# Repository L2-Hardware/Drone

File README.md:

# Drone

# Custom 5-Inch Quadcopter Project

Welcome to the main repository of our custom-built 5-inch FPV drone. This project is a collaborative effort to design, build, and program a high-performance quadcopter completely from scratch, bridging custom mechanical engineering with bespoke hardware and software design.

## Project Overview

Instead of relying on off-the-shelf Flight Controllers (FC) or pre-compiled firmware like Betaflight/ArduPilot, this project aims to build the core systems from the ground up to deeply understand drone flight dynamics, sensor fusion, and real-time embedded systems.

The project is divided into three main domains:
*   **Mechanics & Frame:** Custom 5-inch carbon fiber frame designed from scratch (designed by [Friend's Name]).
*   **Hardware (FC PCB):** A custom-designed Flight Controller board based on the STM32 architecture.
*   **Firmware (MCU):** A custom RTOS-based flight control software written in C/C++.

## System Architecture

*   **Power & Propulsion:** 6S LiPo Battery, custom 4-in-1 ESC (`Hardware/Kicad/ESCV00`, AM32 firmware), and 4x Brushless Motors (2207/2306).
*   **Radio Control:** custom ExpressLRS (ELRS) 2.4GHz receiver (`Hardware/Kicad/RXV00`, ESP32-C3 + SX1281) communicating via CRSF protocol for ultra-low latency.
*   **Video System (FPV):** custom analog 5.8GHz VTx (`Hardware/Kicad/VTXV00`, RTC6705 + RFPA5542) with on-board OSD (AT7456E) on the FC.
*   **Brain:** Custom STM32 Flight Controller (See `/Hardware` and `/Firmware` folders).

## Repository Structure

*   `/Mechanics` - 3D models, CAD files, and CNC routing paths for the frame.
*   `/Hardware` - KiCad projects: flight controller (FCV00), 4-in-1 ESC (ESCV00), ELRS receiver (RXV00), video transmitter (VTXV00).
*   `/Firmware` - STM32 source code, RTOS configuration, and PID algorithms.

## Status
*Active Development* - Currently designing the FC PCB and prototyping the RTOS task scheduler.

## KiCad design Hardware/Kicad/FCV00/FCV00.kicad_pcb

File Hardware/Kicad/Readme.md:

# KiCad projects - drone electronics

## Libraries

If you want a local copy of Kicad Libraries for each board project, inside the KiCad directory run:

git submodule add https://github.com/Loredati-svg/Kicad_Library.git
git commit -m "Added Kicad Libs submodule"
git push

If you don't want a local copy of the libraries for each project but you are ok with having a single local copy of it in a different folder and want to link to it from the board project folder, just run the "bring_libs.bat".
This will create a junction link.

### Part convention (same as B0_EE)

All the parts used by the four boards are in the shared [Kicad_Libs](https://github.com/L2-Hardware/Kicad_Libs)
(`${KIPRJMOD}/../KiCad_Libs/<eLib>`). Every real part is named after its manufacturer part number, and the
symbol, footprint, 3D model and datasheet all carry that name:

```
<eLib>.kicad_sym             symbol      <eLib>:STM32F405RGT6
<eLib>.pretty/               footprint   STM32F405RGT6.kicad_mod
<eLib>.3dshapes/             3D model    STM32F405RGT6.step
datasheet/                   datasheet   STM32F405RGT6.pdf  (README.md: manufacturer and full ordering code)
```

Symbols carry the five standard fields only: Reference, Value (= part name), Footprint, Datasheet
(`${KIPRJMOD}/../KiCad_Libs/<eLib>/datasheet/<part>.pdf`) and Description. Plain passives without a part number
(R, C, LED, L) keep the generic symbol with the value and a package footprint. Test points, mounting holes and
solder jumpers are copper only: no 3D model and not in the BOM.

Where the parts come from:
* **Footprints**: official KiCad libraries, renamed after the part. **3D models**: STEP from KiCad 10.
* **Symbols**: generated in a single style. Pin tables come from the official KiCad symbol of the same part where
  KiCad has one. Otherwise they come from the vendor datasheet (see "Verify before ordering boards").

## Boards

| Project | Board | Size / layers | Main parts |
|---|---|---|---|
| `FCV00` | Flight controller | 36x36 mm, 30.5 mm M3 pattern (4 mm holes for grommets), 4 layers | STM32F405RGT6, ICM-42688-P, LPS22DF, AT7456E OSD, W25Q128JV, 2x TPS54360B (5V 3A / 10V 2A), 2x AP2112K-3.3, USB-C |
| `ESCV00` | 4-in-1 ESC (AM32) | 42x42 mm, 30.5 mm M3 pattern, 6 layers 2 oz recommended | 4x (STM32F051K8U6 or AT32F421K8U7 + DRV8300D + 6x BSZ018N04LS6), 0.25 mOhm shunt + INA181A3, LMR16006 10V gate rail |
| `RXV00` | ExpressLRS 2.4 GHz receiver | 22x14 mm, 4 layers | ESP32-C3FH4 + SX1281, u.FL |
| `VTXV00` | 5.8 GHz analog VTX | 27x27 mm, 20x20 mm M2 pattern, 4 layers | RTC6705 + RFPA5542 (~25 dBm), STM32F031G6U6 / GD32F130G6U6 (OpenVTx) |

```
 6S LiPo ──XT60──► ESCV00 ──(JST-SH 8: VBAT GND CURR TLM M1..M4)──► FCV00 ──(JST-SH 4: 5V GND TX RX)──► RXV00 ── 2.4 GHz antenna
                   │  4x BLDC motors                                  │  ├─(JST-SH 6: 10V 5V GND VIDEO TX RX)──► VTXV00 ── 5.8 GHz antenna
                   └──────────────────────────────────────────────────┘  ├─(JST-SH 3: PWR GND VIDEO)◄── analog FPV camera (bought)
                                                                         ├─ GPS / compass port, AUX UART port, LED strip, buzzer
                                                                         └─ USB-C (configuration / DFU)
```

The connectors are pin-matched, so the harnesses are 1:1 JST-SH cables. Power the FC from the ESC harness only,
not from separate battery wires. Otherwise part of the motor return current flows through the JST ground wire
and bypasses the current shunt.

Bought parts that are not designed here: motors, battery, camera, propellers, antennas, frame.

### Each project contains
* `<NAME>.kicad_sch` - hierarchical schematic (root page = overview + design notes, one sub-sheet per block)
* `<NAME>.kicad_pcb` - board outline, mounting holes, layer count, GND plane on In1, every footprint loaded with
  its nets and linked to its symbol (footprints are parked next to the outline, grouped by sheet)
* `<NAME>.kicad_pro` - net classes (power / gate / RF 50 ohm / USB ...) and JLCPCB-compatible minimum rules
* `<NAME>_BOM.csv` - grouped BOM exported from the schematic with `kicad-cli` (Value = part number for real parts)
* `RXV00/RXV00_hardware.json` - ExpressLRS hardware layout for the receiver

## Validation done
* Every schematic was exported with `kicad-cli`. KiCad's connectivity matches the intended netlist exactly (no
  merged or split nets).
* Every symbol pin maps to a footprint pad. Every footprint pad that needs a net has one.
* KiCad 10 `kicad-cli`: no symbol/footprint library mismatch in ERC or DRC, and schematic/PCB parity is clean
  (fields, footprints, BOM/DNP attributes).

## Verify before ordering boards
Parts whose pin table was typed from a datasheet. Check them against the latest datasheet:

| Part | What to check |
|---|---|
| AT7456E | Uses the MAX7456 pinout. Check the HTSSOP exposed-pad size. |
| SX1281IMLTRT | Pin table from Semtech DS rev 3.x. RF matching values are starting points (tune with a VNA). |
| RTC6705 | Pin table from `eRFModule/datasheet/RTC6705.pdf`. The exposed-pad size is not given (QFN-40 6x6, EP 4.6 assumed). Loop filter, output match and the BUFVDD power-control path are starting points. |
| DRV8300DRGER | Pin table from the TI datasheet. Check the RGE exposed-pad size. |
| ICM-42688-P | Pin table from the KiCad IIM-42652 symbol (same LGA-14 package). Check the RESV pins. |
| BSZ018N04LS6ATMA1 | NexFET SON3.3 land pattern reused. Compare with Infineon's PG-TSDSON-8 FL footprint. |
| TPS54360BDDAR | The compensation network is a starting point. Run TI WEBENCH for the final values. |
| X201652MOB4SI | SX1280 reference crystal: 52 MHz, +/-10 ppm. |

Part numbers that could not be found in the manufacturer catalogue: confirm or replace them before ordering.

| Part | Note |
|---|---|
| X322508MLB4SI, X201640MLB4SI, X201652MOB4SI | Not listed by YXC/LCSC. The stored datasheet is the YXC SMD3225 / SMD2016 series sheet. |
| LQM21PN150MC0 | Not in the Murata LQM21PN range (which stops below 15 uH). No datasheet stored. |
| WSLP2512R0010FEA | 1 mOhm WSLP2512: check availability; the stored datasheet is the Vishay WSLP series sheet. |
| SWPA3012S100MT, PMEG3020EH | Datasheet not stored (the vendor site blocks downloads): the Datasheet field links to it. |

Passive, crystal and LED part numbers are suggestions: confirm them (stock, load capacitance, voltage rating) at
your distributor or assembler.

## Next steps
1. Open each project, run ERC.
2. PCB: place the parts (connectors on the edges, IMU away from the bucks, short power loops), then route.
   Use 50 ohm coplanar lines on RXV00/VTXV00 and a full GND plane under the RF parts. On ESCV00, use wide
   polygons for VBAT/phases and thermal vias. Run DRC.
3. Order from JLCPCB / PCBWay: gerbers + BOM + placement file, assembly (ESC 6 layers 2 oz).
4. Bring-up order: power rails, then SWD/DFU, then each sensor, then radio links.

## Firmware notes
* **FCV00**: pin map on the root sheet (gyro SPI1 + external 32 kHz CLKIN on PB0, OSD SPI2, flash SPI3,
  motors TIM8 CH1-4 on PC6-PC9).
* **ESCV00**: AM32. With F051, use `HARDWARE_GROUP_F0_B`. With AT32F421, use `HARDWARE_GROUP_AT_B` +
  `HARDWARE_GROUP_AT_045` (same pinout as `TBS_6S_4IN1_F421`). Flash the bootloader per MCU through the SWD pads
  once.
* **RXV00**: ExpressLRS `Unified_ESP32C3_2400_RX` + `RXV00_hardware.json` (based on "Generic C3 2400").
* **VTXV00**: OpenVTx `Generic_GD32F130` pinout (populate GD32F130G6U6), or your own firmware on the STM32F031.
  Up to 25 mW EIRP is licence-free in the EU. Higher power needs an amateur radio licence.

## Regenerating
`tools/gen/` holds the scripts that produced the libraries, schematics, BOMs and PCB set-up:
`build.py` (libraries + schematics + BOM), `check.py` (connectivity check) and `pcbgen.py` (PCB set-up).
**Re-running them overwrites the project files.** They are a starting point: once you start editing in KiCad,
KiCad is the master. They still produce the old generic part names, so do not re-run them on these boards.

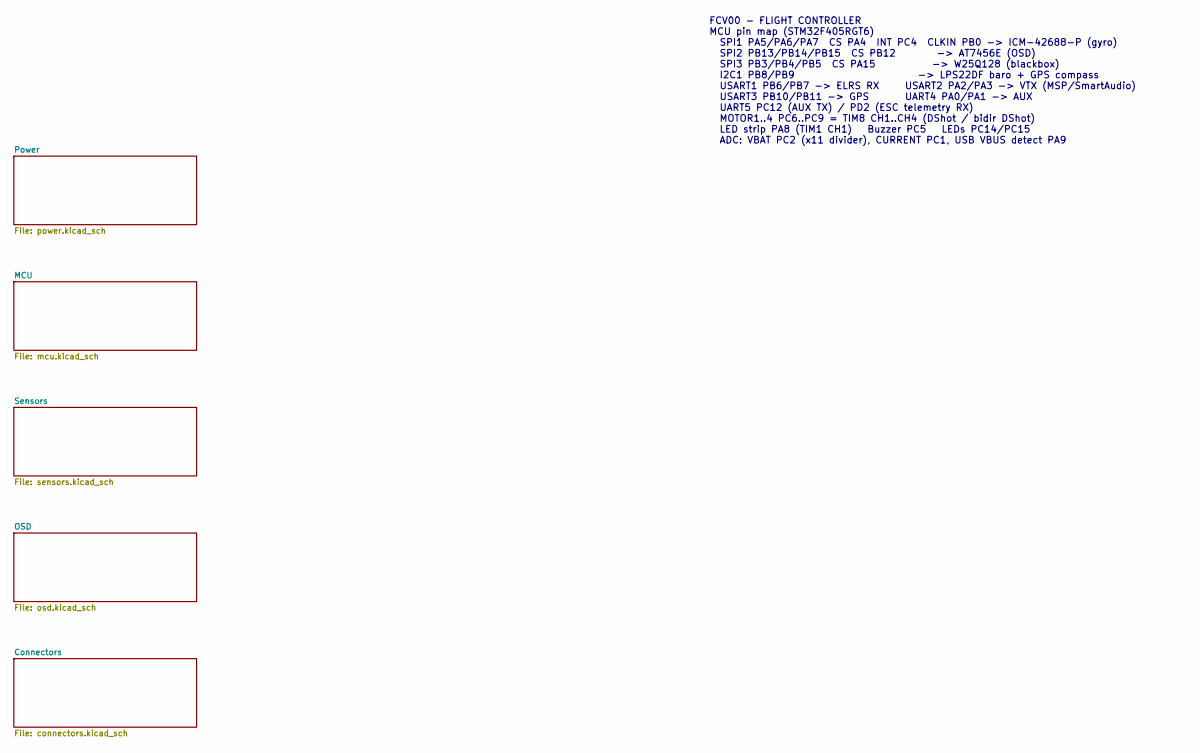
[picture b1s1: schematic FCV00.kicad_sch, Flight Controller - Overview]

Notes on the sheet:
FCV00 - FLIGHT CONTROLLER MCU pin map (STM32F405RGT6) SPI1 PA5/PA6/PA7 CS PA4 INT PC4 CLKIN PB0 -> ICM-42688-P (gyro) SPI2 PB13/PB14/PB15 CS PB12 -> AT7456E (OSD) SPI3 PB3/PB4/PB5 CS PA15 -> W25Q128 (blackbox) I2C1 PB8/PB9 -> LPS22DF baro + GPS compass USART1 PB6/PB7 -> ELRS RX USART2 PA2/PA3 -> VT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

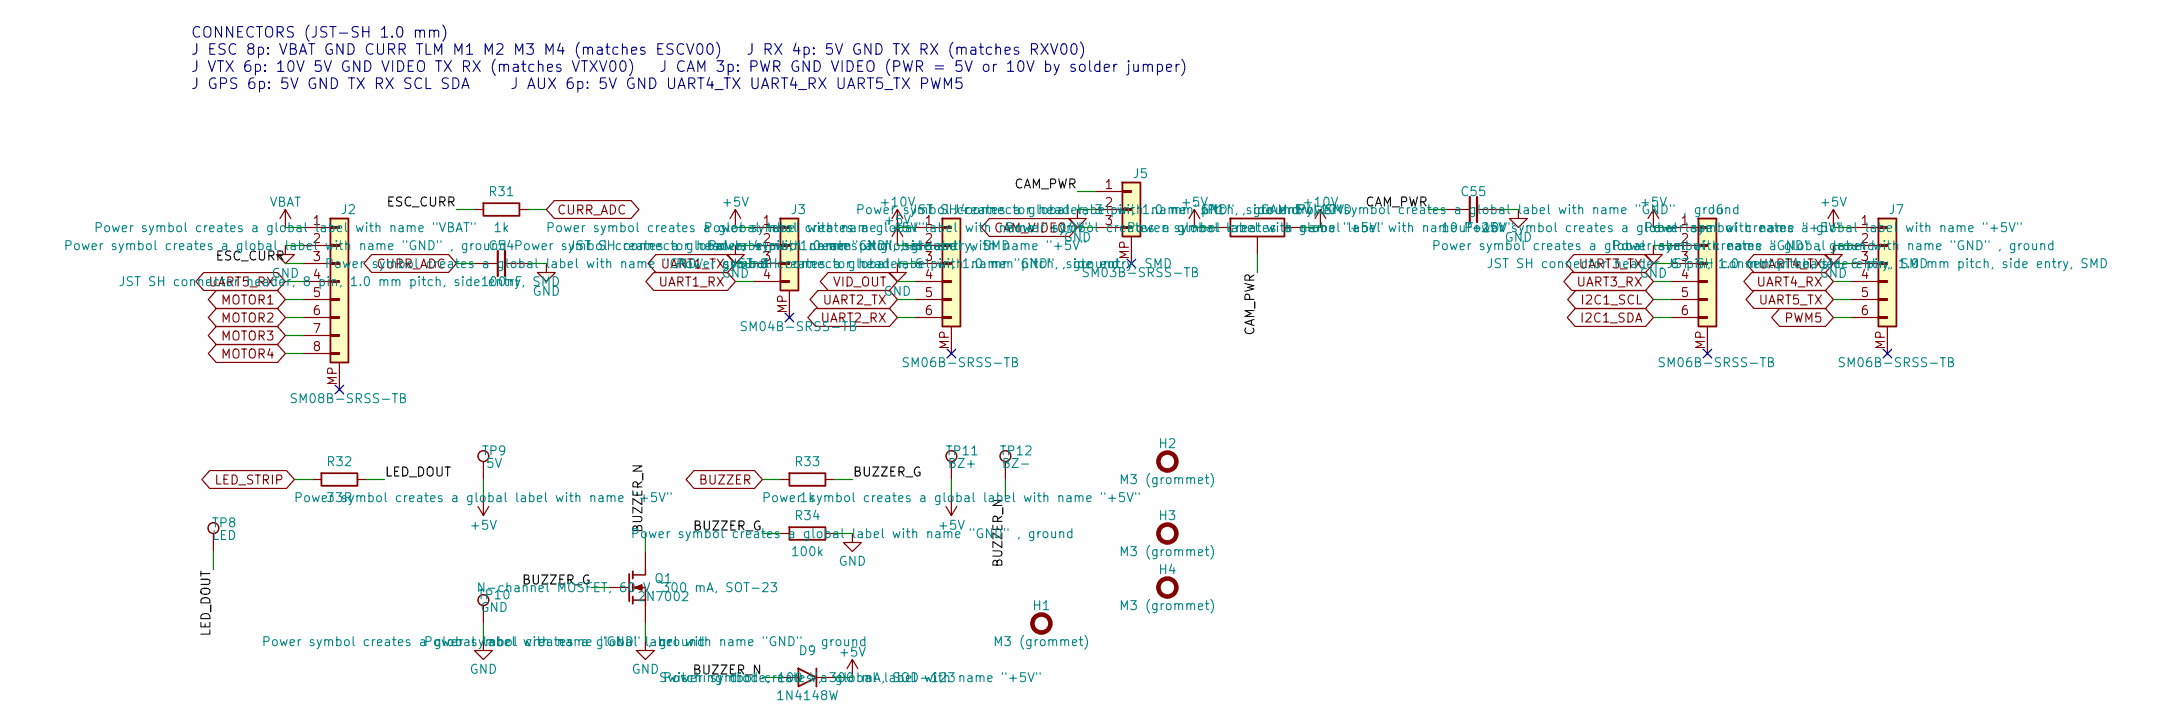
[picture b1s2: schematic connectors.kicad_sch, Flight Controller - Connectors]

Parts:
C54: 100nF; C_0402_1005Metric
C55: 10uF 25V; C_0805_2012Metric
D9: 1N4148W
H1, H2, H3, H4: M3 (grommet); MountingHole_4mm
J2: SM08B-SRSS-TB
J3: SM04B-SRSS-TB
J4, J6, J7: SM06B-SRSS-TB
J5: SM03B-SRSS-TB
JP1: CAM 5V|10V; SolderJumper-3_P1.3mm_Open_RoundedPad1.0x1.5mm
Q1: 2N7002
R31, R33: 1k; R_0402_1005Metric
R32: 33R; R_0402_1005Metric
R34: 100k; R_0402_1005Metric
TP8: LED; TestPoint_Pad_2.0x2.0mm
TP9: 5V; TestPoint_Pad_2.0x2.0mm
TP10: GND; TestPoint_Pad_2.0x2.0mm
TP11: BZ+; TestPoint_Pad_2.0x2.0mm
TP12: BZ-; TestPoint_Pad_2.0x2.0mm

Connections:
+5V: D9.1 (K), J3.1, J4.2, J6.1, J7.1, JP1.1 (A), TP9.1, TP11.1; also elsewhere on the board
+10V: J4.1, JP1.3 (B); also elsewhere on the board
/Connectors/BUZZER_G: Q1.1 (G), R33.2, R34.1
/Connectors/BUZZER_N: D9.2 (A), Q1.3 (D), TP12.1
/Connectors/CAM_PWR: C55.1, J5.1, JP1.2 (C)
/Connectors/ESC_CURR: J2.3, R31.1
/Connectors/LED_DOUT: R32.2, TP8.1
BUZZER: R33.1; also elsewhere on the board
CAM_VIDEO: J5.3; also elsewhere on the board
CURR_ADC: C54.1, R31.2; also elsewhere on the board
GND: C54.2, C55.2, J2.2, J3.2, J4.3, J5.2, J6.2, J7.2, Q1.2 (S), R34.2, TP10.1; also elsewhere on the board
I2C1_SCL: J6.5; also elsewhere on the board
I2C1_SDA: J6.6; also elsewhere on the board
LED_STRIP: R32.1; also elsewhere on the board
MOTOR1: J2.5; also elsewhere on the board
MOTOR2: J2.6; also elsewhere on the board
MOTOR3: J2.7; also elsewhere on the board
MOTOR4: J2.8; also elsewhere on the board
PWM5: J7.6; also elsewhere on the board
UART1_RX: J3.4; also elsewhere on the board
UART1_TX: J3.3; also elsewhere on the board
UART2_RX: J4.6; also elsewhere on the board
UART2_TX: J4.5; also elsewhere on the board
UART3_RX: J6.4; also elsewhere on the board
UART3_TX: J6.3; also elsewhere on the board
UART4_RX: J7.4; also elsewhere on the board
UART4_TX: J7.3; also elsewhere on the board
UART5_RX: J2.4; also elsewhere on the board
UART5_TX: J7.5; also elsewhere on the board
VBAT: J2.1; also elsewhere on the board
VID_OUT: J4.4; also elsewhere on the board

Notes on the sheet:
CONNECTORS (JST-SH 1.0 mm) J ESC 8p: VBAT GND CURR TLM M1 M2 M3 M4 (matches ESCV00) J RX 4p: 5V GND TX RX (matches RXV00) J VTX 6p: 10V 5V GND VIDEO TX RX (matches VTXV00) J CAM 3p: PWR GND VIDEO (PWR = 5V or 10V by solder jumper) J GPS 6p: 5V GND TX RX SCL SDA J AUX 6p: 5V GND UART4_TX UART4_RX UA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

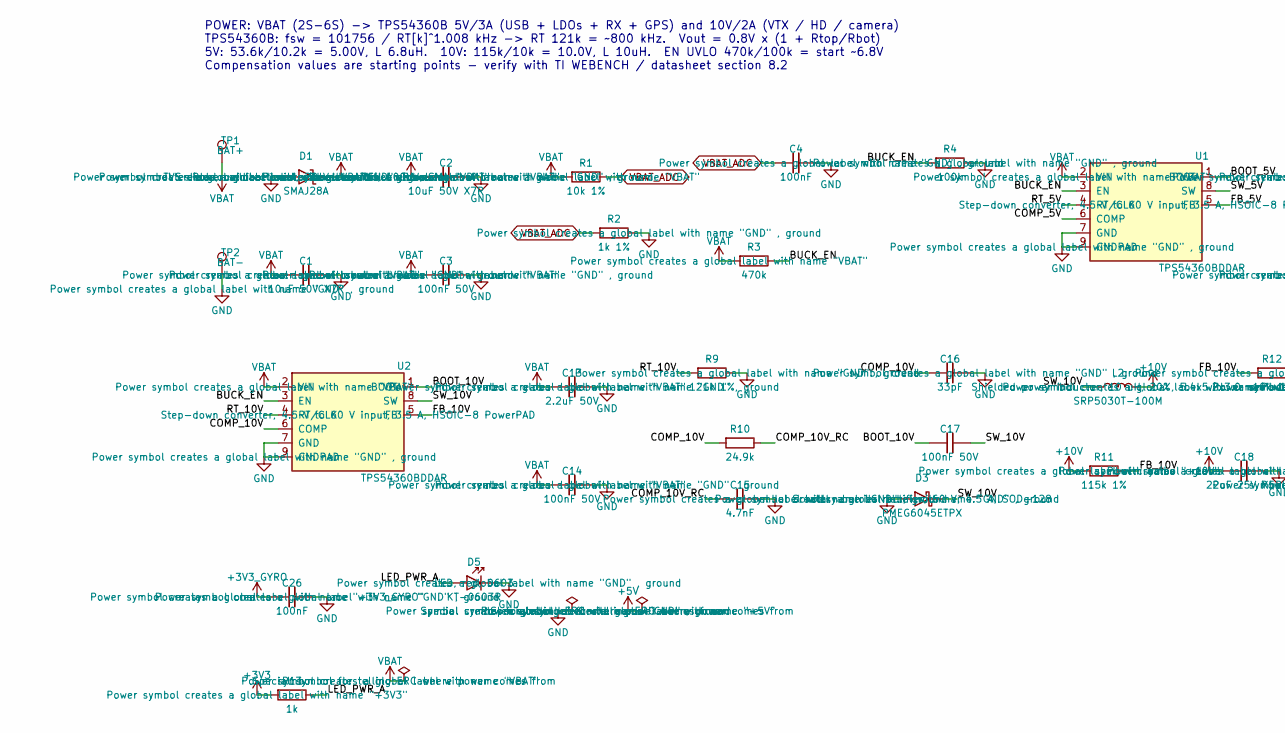
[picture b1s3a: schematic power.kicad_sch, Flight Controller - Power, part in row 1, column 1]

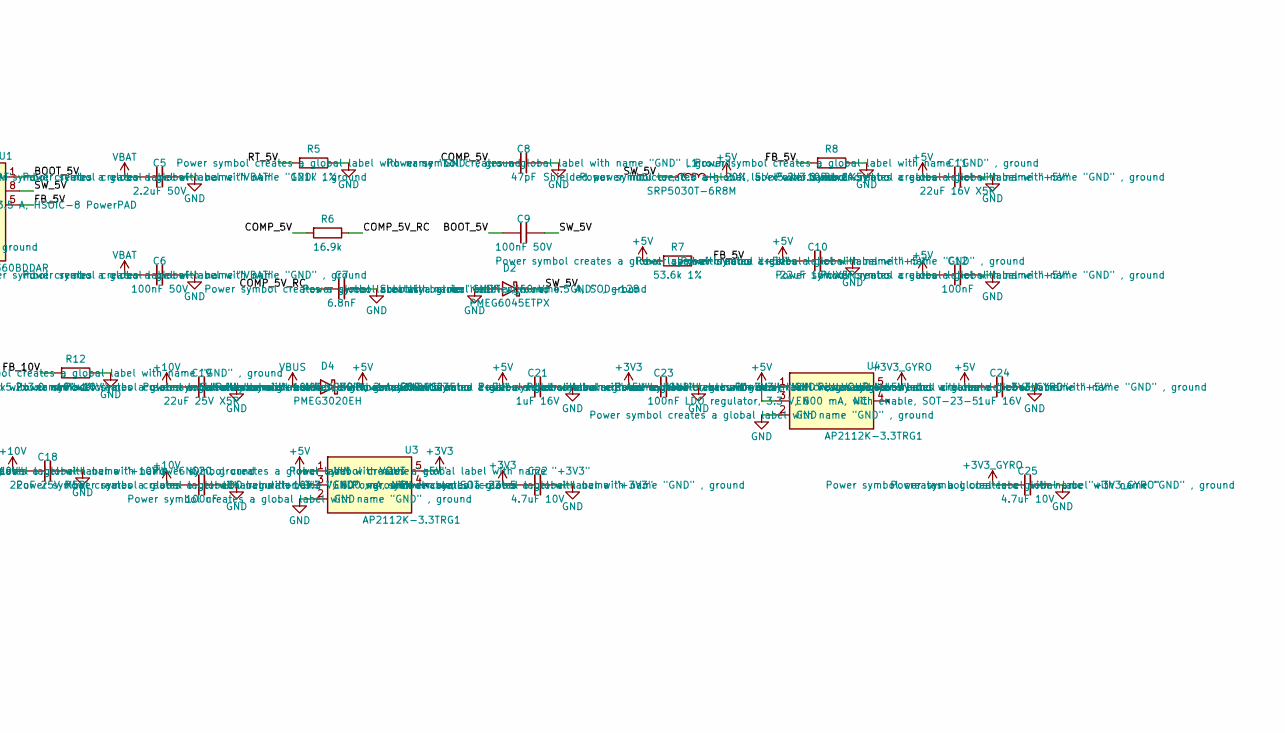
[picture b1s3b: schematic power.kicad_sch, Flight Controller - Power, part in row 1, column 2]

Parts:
C1, C2: 10uF 50V X7R; C_1206_3216Metric
C3, C6, C9, C14, C17: 100nF 50V; C_0603_1608Metric
C4, C12, C20, C23, C26: 100nF; C_0402_1005Metric
C5, C13: 2.2uF 50V; C_0805_2012Metric
C7: 6.8nF; C_0402_1005Metric
C8: 47pF; C_0402_1005Metric
C10, C11: 22uF 16V X5R; C_0805_2012Metric
C15: 4.7nF; C_0402_1005Metric
C16: 33pF; C_0402_1005Metric
C18, C19: 22uF 25V X5R; C_1206_3216Metric
C21, C24: 1uF 16V; C_0402_1005Metric
C22, C25: 4.7uF 10V; C_0603_1608Metric
D1: SMAJ28A
D2, D3: PMEG6045ETPX
D4: PMEG3020EH
D5: KT-0603R
L1: SRP5030T-6R8M
L2: SRP5030T-100M
R1, R12: 10k 1%; R_0402_1005Metric
R2: 1k 1%; R_0402_1005Metric
R3: 470k; R_0402_1005Metric
R4: 100k; R_0402_1005Metric
R5, R9: 121k 1%; R_0402_1005Metric
R6: 16.9k; R_0402_1005Metric
R7: 53.6k 1%; R_0402_1005Metric
R8: 10.2k 1%; R_0402_1005Metric
R10: 24.9k; R_0402_1005Metric
R11: 115k 1%; R_0402_1005Metric
R13: 1k; R_0402_1005Metric
TP1: BAT+; SolderPad_3x5mm
TP2: BAT-; SolderPad_3x5mm
U1, U2: TPS54360BDDAR
U3, U4: AP2112K-3.3TRG1

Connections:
+3V3: C22.1, C23.1, R13.1, U3.5 (VOUT); also elsewhere on the board
+3V3_GYRO: C25.1, C26.1, U4.5 (VOUT); also elsewhere on the board
+5V: C10.1, C11.1, C12.1, C21.1, C24.1, D4.1 (K), L1.2, R7.1, U3.1 (VIN), U3.3 (EN), U4.1 (VIN), U4.3 (EN); also elsewhere on the board
+10V: C18.1, C19.1, C20.1, L2.2, R11.1; also elsewhere on the board
/Power/BOOT_5V: C9.1, U1.1 (BOOT)
/Power/BOOT_10V: C17.1, U2.1 (BOOT)
/Power/BUCK_EN: R3.2, R4.1, U1.3 (EN), U2.3 (EN)
/Power/COMP_5V: C8.1, R6.1, U1.6 (COMP)
/Power/COMP_5V_RC: C7.1, R6.2
/Power/COMP_10V: C16.1, R10.1, U2.6 (COMP)
/Power/COMP_10V_RC: C15.1, R10.2
/Power/FB_5V: R7.2, R8.1, U1.5 (FB)
/Power/FB_10V: R11.2, R12.1, U2.5 (FB)
/Power/LED_PWR_A: D5.2 (A), R13.2
/Power/RT_5V: R5.1, U1.4 (RT/CLK)
/Power/RT_10V: R9.1, U2.4 (RT/CLK)
/Power/SW_5V: C9.2, D2.1 (K), L1.1, U1.8 (SW)
/Power/SW_10V: C17.2, D3.1 (K), L2.1, U2.8 (SW)
GND: C1.2, C2.2, C3.2, C4.2, C5.2, C6.2, C7.2, C8.2, C10.2, C11.2, C12.2, C13.2, C14.2, C15.2, C16.2, C18.2, C19.2, C20.2, C21.2, C22.2, C23.2, C24.2, C25.2, C26.2, D1.2 (A), D2.2 (A), D3.2 (A), D5.1 (K), R2.2, R4.2, R5.2, R8.2, R9.2, R12.2, TP2.1, U1.7 (GND), U1.9 (GNDPAD), U2.7 (GND), U2.9 (GNDPAD), U3.2 (GND), U4.2 (GND); also elsewhere on the board
VBAT: C1.1, C2.1, C3.1, C5.1, C6.1, C13.1, C14.1, D1.1 (K), R1.1, R3.1, TP1.1, U1.2 (VIN), U2.2 (VIN); also elsewhere on the board
VBAT_ADC: C4.1, R1.2, R2.1; also elsewhere on the board
VBUS: D4.2 (A); also elsewhere on the board

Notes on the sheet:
POWER: VBAT (2S-6S) -> TPS54360B 5V/3A (USB + LDOs + RX + GPS) and 10V/2A (VTX / HD / camera) TPS54360B: fsw = 101756 / RT[k]^1.008 kHz -> RT 121k = ~800 kHz. Vout = 0.8V x (1 + Rtop/Rbot) 5V: 53.6k/10.2k = 5.00V, L 6.8uH. 10V: 115k/10k = 10.0V, L 10uH. EN UVLO 470k/100k = start ~6.8V Compensation 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

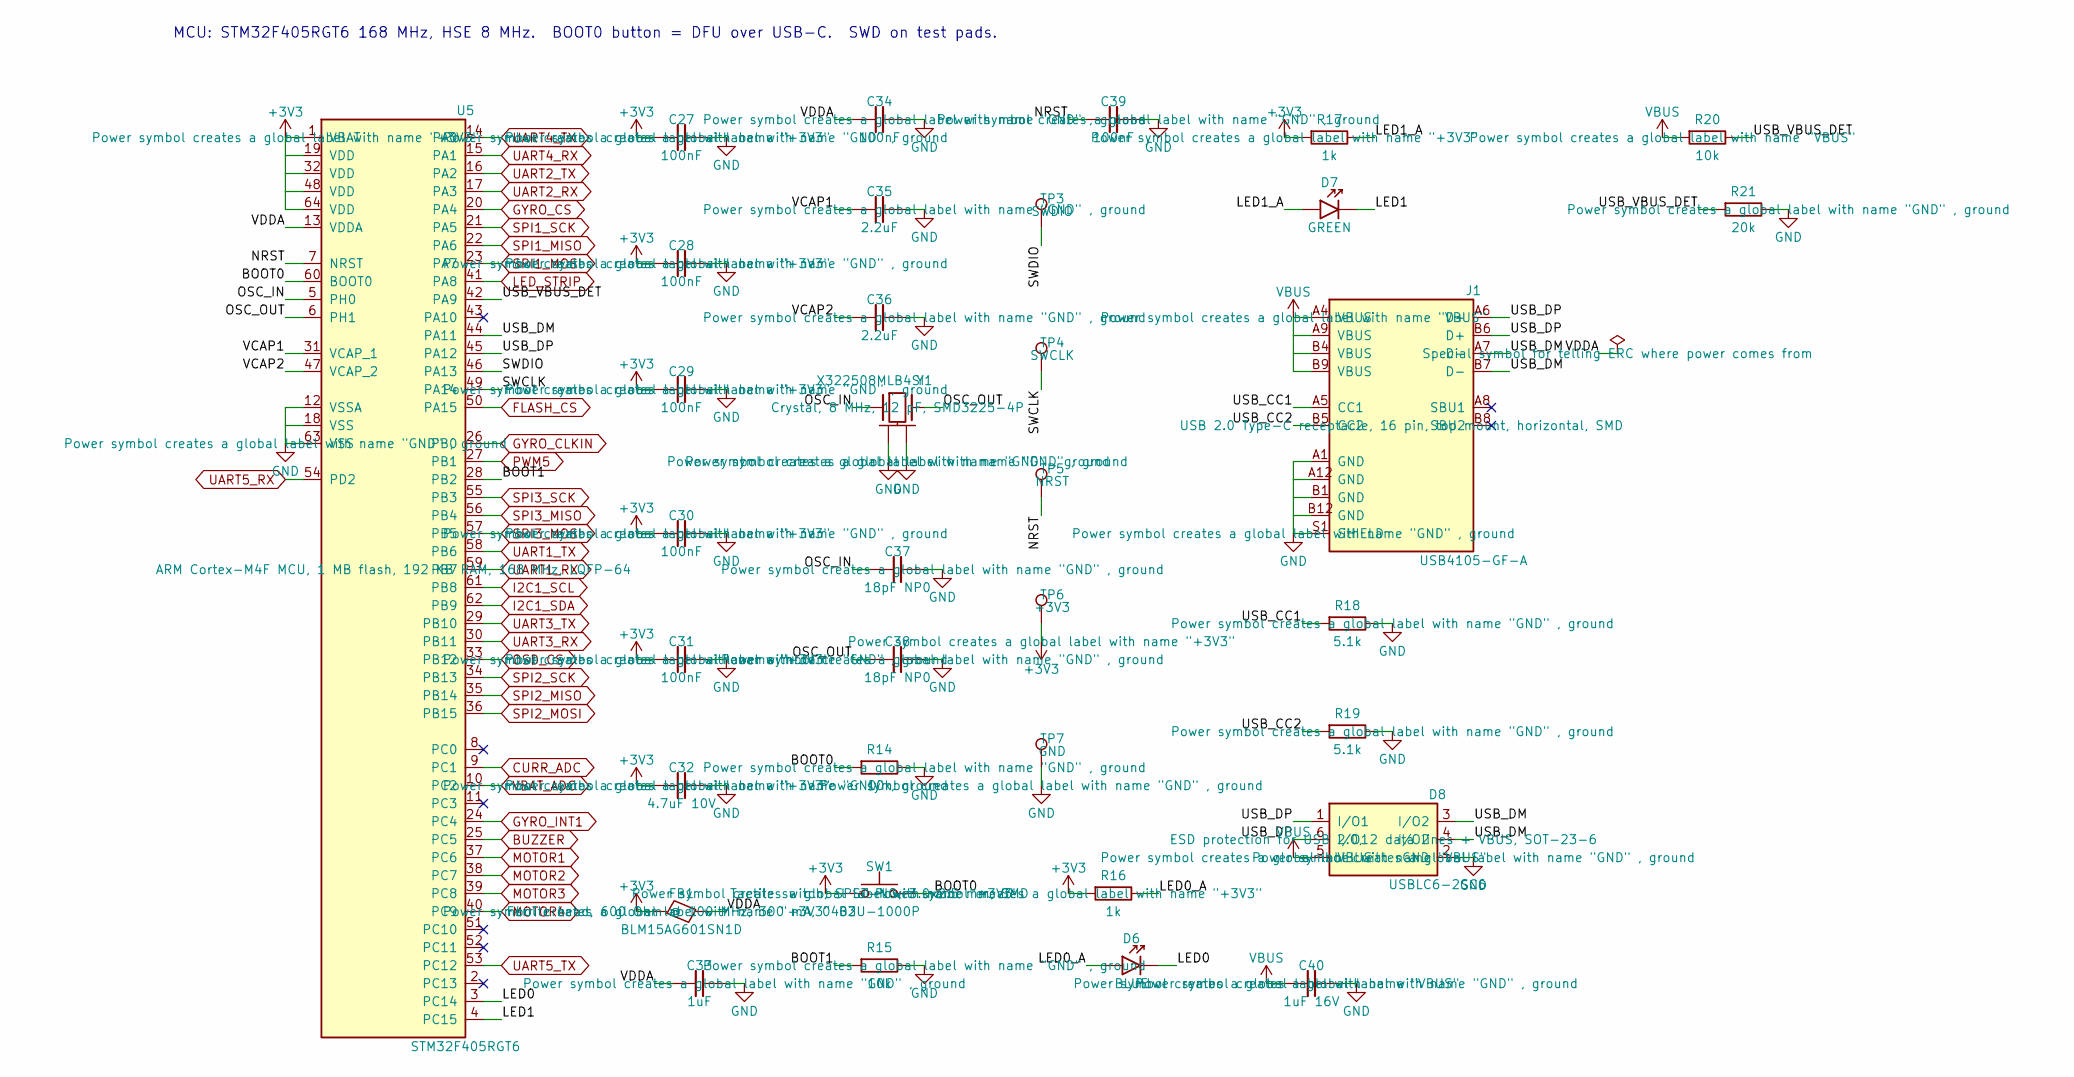
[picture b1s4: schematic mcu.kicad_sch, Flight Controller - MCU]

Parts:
C27, C28, C29, C30, C31, C34, C39: 100nF; C_0402_1005Metric
C32: 4.7uF 10V; C_0603_1608Metric
C33: 1uF; C_0402_1005Metric
C35, C36: 2.2uF; C_0402_1005Metric
C37, C38: 18pF NP0; C_0402_1005Metric
C40: 1uF 16V; C_0402_1005Metric
D6: BLUE; LED_0603_1608Metric
D7: GREEN; LED_0603_1608Metric
D8: USBLC6-2SC6
FB1: BLM15AG601SN1D
J1: USB4105-GF-A
R14, R15, R20: 10k; R_0402_1005Metric
R16, R17: 1k; R_0402_1005Metric
R18, R19: 5.1k; R_0402_1005Metric
R21: 20k; R_0402_1005Metric
SW1: B3U-1000P
TP3: SWDIO; TestPoint_Pad_D1.0mm
TP4: SWCLK; TestPoint_Pad_D1.0mm
TP5: NRST; TestPoint_Pad_D1.0mm
TP6: +3V3; TestPoint_Pad_D1.0mm
TP7: GND; TestPoint_Pad_D1.0mm
U5: STM32F405RGT6
Y1: X322508MLB4SI

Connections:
+3V3: C27.1, C28.1, C29.1, C30.1, C31.1, C32.1, FB1.1, R16.1, R17.1, SW1.1, TP6.1, U5.1 (VBAT), U5.19 (VDD), U5.32 (VDD), U5.48 (VDD), U5.64 (VDD); also elsewhere on the board
/MCU/BOOT0: R14.1, SW1.2, U5.60 (BOOT0)
/MCU/BOOT1: R15.1, U5.28 (PB2)
/MCU/LED0: D6.1 (K), U5.3 (PC14)
/MCU/LED0_A: D6.2 (A), R16.2
/MCU/LED1: D7.1 (K), U5.4 (PC15)
/MCU/LED1_A: D7.2 (A), R17.2
/MCU/NRST: C39.1, TP5.1, U5.7 (NRST)
/MCU/OSC_IN: C37.1, U5.5 (PH0), Y1.1
/MCU/OSC_OUT: C38.1, U5.6 (PH1), Y1.3
/MCU/SWCLK: TP4.1, U5.49 (PA14)
/MCU/SWDIO: TP3.1, U5.46 (PA13)
/MCU/USB_CC1: J1.A5 (CC1), R18.1
/MCU/USB_CC2: J1.B5 (CC2), R19.1
/MCU/USB_DM: D8.3 (I/O2), D8.4 (I/O2), J1.A7 (D-), J1.B7 (D-), U5.44 (PA11)
/MCU/USB_DP: D8.1 (I/O1), D8.6 (I/O1), J1.A6 (D+), J1.B6 (D+), U5.45 (PA12)
/MCU/USB_VBUS_DET: R20.2, R21.1, U5.42 (PA9)
/MCU/VCAP1: C35.1, U5.31 (VCAP_1)
/MCU/VCAP2: C36.1, U5.47 (VCAP_2)
/MCU/VDDA: C33.1, C34.1, FB1.2, U5.13 (VDDA)
BUZZER: U5.25 (PC5); also elsewhere on the board
CURR_ADC: U5.9 (PC1); also elsewhere on the board
FLASH_CS: U5.50 (PA15); also elsewhere on the board
GND: C27.2, C28.2, C29.2, C30.2, C31.2, C32.2, C33.2, C34.2, C35.2, C36.2, C37.2, C38.2, C39.2, C40.2, D8.2 (GND), J1.A1 (GND), J1.A12 (GND), J1.B1 (GND), J1.B12 (GND), J1.S1 (SHIELD), R14.2, R15.2, R18.2, R19.2, R21.2, TP7.1, U5.12 (VSSA), U5.18 (VSS), U5.63 (VSS), Y1.2 (GND), Y1.4 (GND); also elsewhere on the board
GYRO_CLKIN: U5.26 (PB0); also elsewhere on the board
GYRO_CS: U5.20 (PA4); also elsewhere on the board
GYRO_INT1: U5.24 (PC4); also elsewhere on the board
I2C1_SCL: U5.61 (PB8); also elsewhere on the board
I2C1_SDA: U5.62 (PB9); also elsewhere on the board
LED_STRIP: U5.41 (PA8); also elsewhere on the board
MOTOR1: U5.37 (PC6); also elsewhere on the board
MOTOR2: U5.38 (PC7); also elsewhere on the board
MOTOR3: U5.39 (PC8); also elsewhere on the board
MOTOR4: U5.40 (PC9); also elsewhere on the board
OSD_CS: U5.33 (PB12); also elsewhere on the board
PWM5: U5.27 (PB1); also elsewhere on the board
SPI1_MISO: U5.22 (PA6); also elsewhere on the board
SPI1_MOSI: U5.23 (PA7); also elsewhere on the board
SPI1_SCK: U5.21 (PA5); also elsewhere on the board
SPI2_MISO: U5.35 (PB14); also elsewhere on the board
SPI2_MOSI: U5.36 (PB15); also elsewhere on the board
SPI2_SCK: U5.34 (PB13); also elsewhere on the board
SPI3_MISO: U5.56 (PB4); also elsewhere on the board
SPI3_MOSI: U5.57 (PB5); also elsewhere on the board
SPI3_SCK: U5.55 (PB3); also elsewhere on the board
UART1_RX: U5.59 (PB7); also elsewhere on the board
UART1_TX: U5.58 (PB6); also elsewhere on the board
UART2_RX: U5.17 (PA3); also elsewhere on the board
UART2_TX: U5.16 (PA2); also elsewhere on the board
UART3_RX: U5.30 (PB11); also elsewhere on the board
UART3_TX: U5.29 (PB10); also elsewhere on the board
UART4_RX: U5.15 (PA1); also elsewhere on the board
UART4_TX: U5.14 (PA0); also elsewhere on the board
UART5_RX: U5.54 (PD2); also elsewhere on the board
UART5_TX: U5.53 (PC12); also elsewhere on the board
VBAT_ADC: U5.10 (PC2); also elsewhere on the board
VBUS: C40.1, D8.5 (VBUS), J1.A4 (VBUS), J1.A9 (VBUS), J1.B4 (VBUS), J1.B9 (VBUS), R20.1; also elsewhere on the board

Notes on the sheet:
MCU: STM32F405RGT6 168 MHz, HSE 8 MHz. BOOT0 button = DFU over USB-C. SWD on test pads.

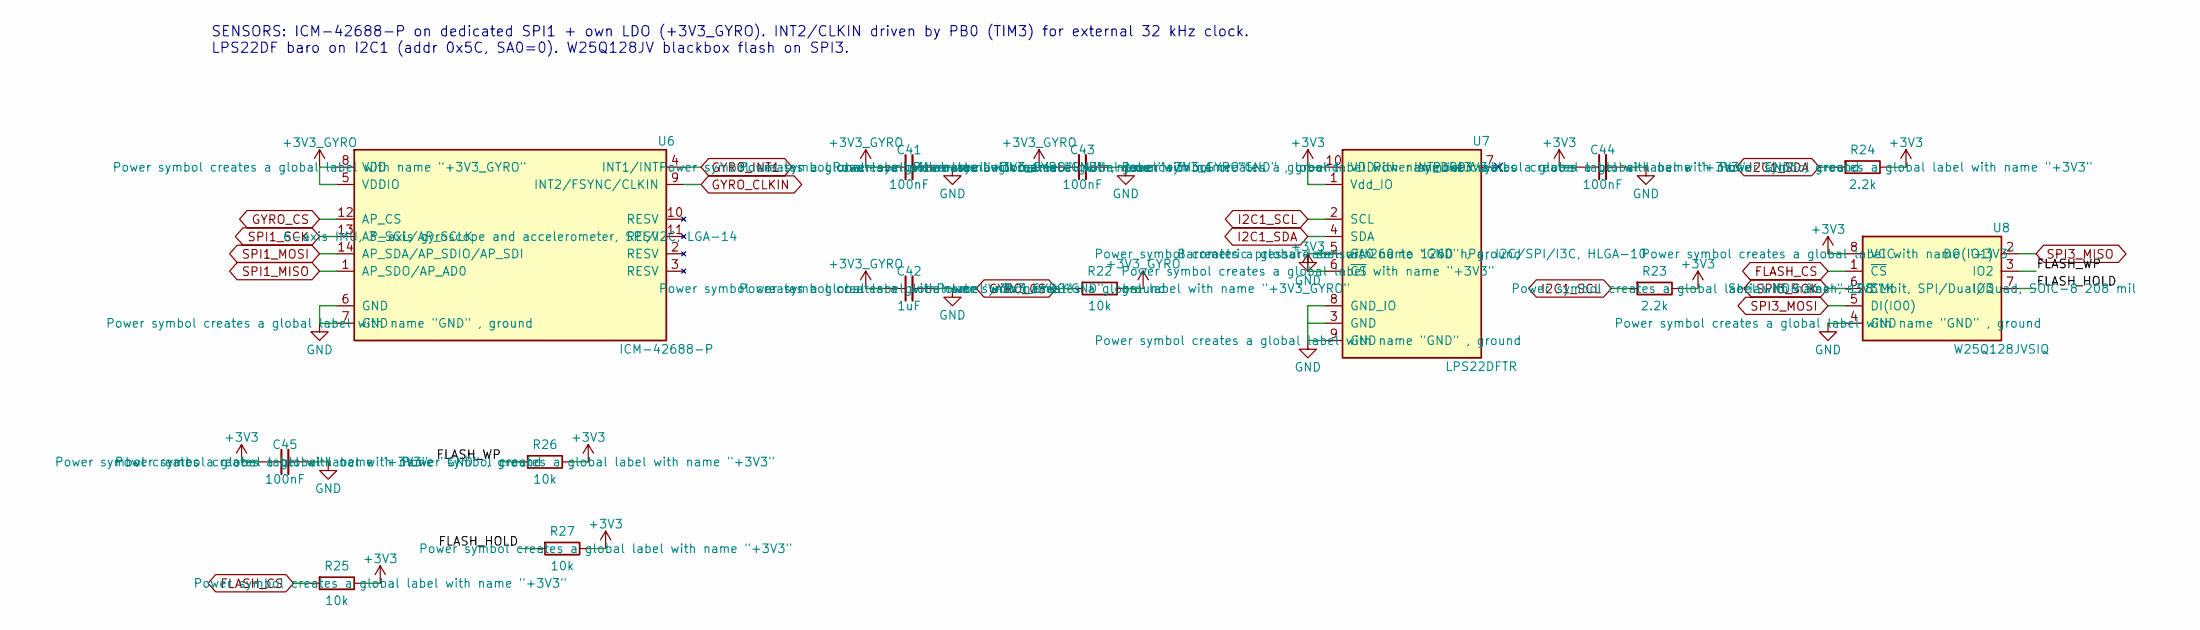
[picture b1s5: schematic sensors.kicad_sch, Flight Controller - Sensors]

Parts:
C41, C43, C44, C45: 100nF; C_0402_1005Metric
C42: 1uF; C_0402_1005Metric
R22, R25, R26, R27: 10k; R_0402_1005Metric
R23, R24: 2.2k; R_0402_1005Metric
U6: ICM-42688-P
U7: LPS22DFTR
U8: W25Q128JVSIQ

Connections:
+3V3: C44.1, C45.1, R23.2, R24.2, R25.2, R26.2, R27.2, U7.1 (Vdd_IO), U7.6 (~CS), U7.10 (VDD), U8.8 (VCC); also elsewhere on the board
+3V3_GYRO: C41.1, C42.1, C43.1, R22.2, U6.5 (VDDIO), U6.8 (VDD); also elsewhere on the board
/Sensors/FLASH_HOLD: R27.1, U8.7 (IO3)
/Sensors/FLASH_WP: R26.1, U8.3 (IO2)
FLASH_CS: R25.1, U8.1 (~CS); also elsewhere on the board
GND: C41.2, C42.2, C43.2, C44.2, C45.2, U6.6 (GND), U6.7 (GND), U7.3 (GND), U7.5 (SA0), U7.8 (GND_IO), U7.9 (GND), U8.4 (GND); also elsewhere on the board
GYRO_CLKIN: U6.9 (INT2/FSYNC/CLKIN); also elsewhere on the board
GYRO_CS: R22.1, U6.12 (AP_CS); also elsewhere on the board
GYRO_INT1: U6.4 (INT1/INT); also elsewhere on the board
I2C1_SCL: R23.1, U7.2 (SCL); also elsewhere on the board
I2C1_SDA: R24.1, U7.4 (SDA); also elsewhere on the board
SPI1_MISO: U6.1 (AP_SDO/AP_AD0); also elsewhere on the board
SPI1_MOSI: U6.14 (AP_SDA/AP_SDIO/AP_SDI); also elsewhere on the board
SPI1_SCK: U6.13 (AP_SCL/AP_SCLK); also elsewhere on the board
SPI3_MISO: U8.2 (DO(IO1)); also elsewhere on the board
SPI3_MOSI: U8.5 (DI(IO0)); also elsewhere on the board
SPI3_SCK: U8.6 (CLK); also elsewhere on the board

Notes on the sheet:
SENSORS: ICM-42688-P on dedicated SPI1 + own LDO (+3V3_GYRO). INT2/CLKIN driven by PB0 (TIM3) for external 32 kHz clock. LPS22DF baro on I2C1 (addr 0x5C, SA0=0). W25Q128JV blackbox flash on SPI3.

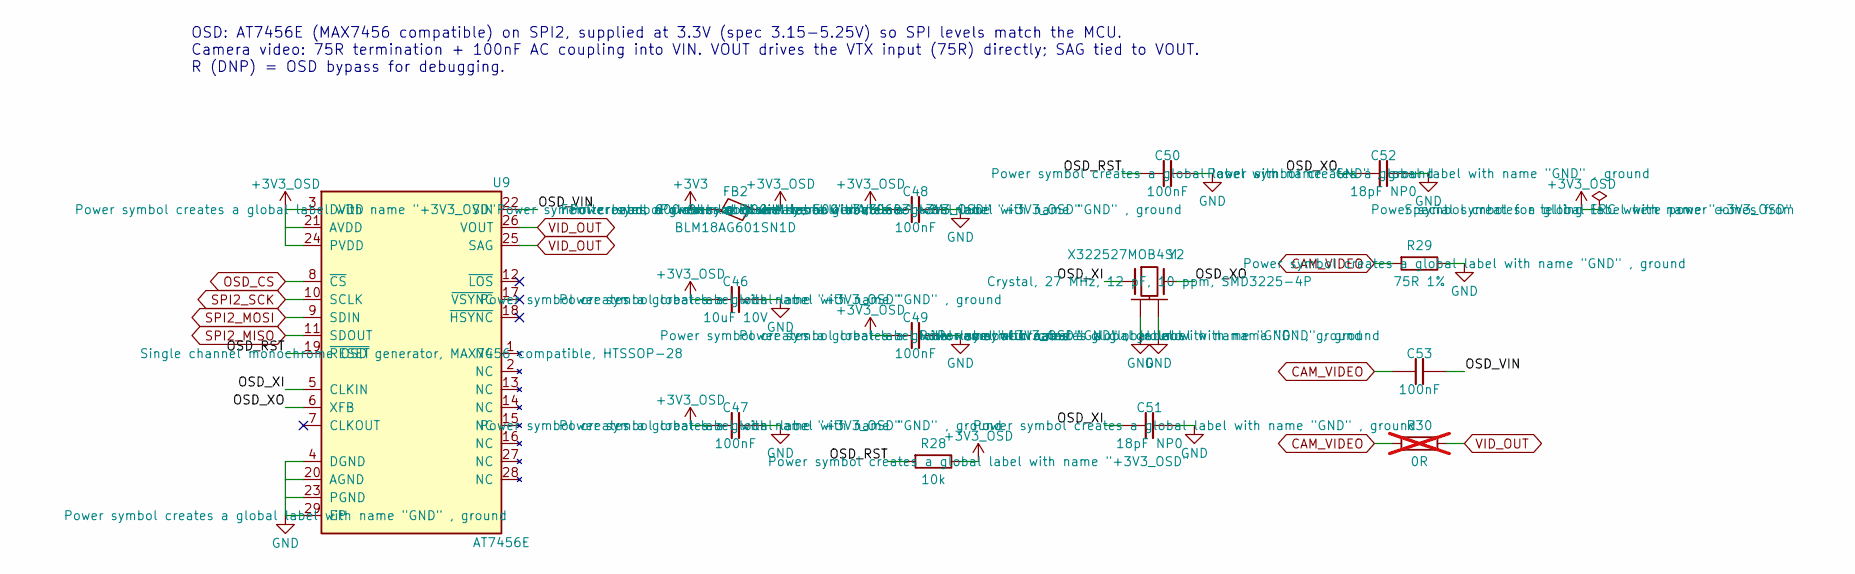
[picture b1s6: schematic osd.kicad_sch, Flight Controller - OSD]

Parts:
C46: 10uF 10V; C_0603_1608Metric
C47, C48, C49, C50, C53: 100nF; C_0402_1005Metric
C51, C52: 18pF NP0; C_0402_1005Metric
FB2: BLM18AG601SN1D
R28: 10k; R_0402_1005Metric
R29: 75R 1%; R_0402_1005Metric
R30: 0R; R_0402_1005Metric; not fitted
U9: AT7456E
Y2: X322527MOB4SI

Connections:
+3V3: FB2.1; also elsewhere on the board
+3V3_OSD: C46.1, C47.1, C48.1, C49.1, FB2.2, R28.2, U9.3 (DVDD), U9.21 (AVDD), U9.24 (PVDD)
/OSD/OSD_RST: C50.1, R28.1, U9.19 (~RESET)
/OSD/OSD_VIN: C53.2, U9.22 (VIN)
/OSD/OSD_XI: C51.1, U9.5 (CLKIN), Y2.1
/OSD/OSD_XO: C52.1, U9.6 (XFB), Y2.3
CAM_VIDEO: C53.1, R29.1, R30.1; also elsewhere on the board
GND: C46.2, C47.2, C48.2, C49.2, C50.2, C51.2, C52.2, R29.2, U9.4 (DGND), U9.20 (AGND), U9.23 (PGND), U9.29 (EP), Y2.2 (GND), Y2.4 (GND); also elsewhere on the board
OSD_CS: U9.8 (~CS); also elsewhere on the board
SPI2_MISO: U9.11 (SDOUT); also elsewhere on the board
SPI2_MOSI: U9.9 (SDIN); also elsewhere on the board
SPI2_SCK: U9.10 (SCLK); also elsewhere on the board
VID_OUT: R30.2, U9.25 (SAG), U9.26 (VOUT); also elsewhere on the board

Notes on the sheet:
OSD: AT7456E (MAX7456 compatible) on SPI2, supplied at 3.3V (spec 3.15-5.25V) so SPI levels match the MCU. Camera video: 75R termination + 100nF AC coupling into VIN. VOUT drives the VTX input (75R) directly; SAG tied to VOUT. R (DNP) = OSD bypass for debugging.

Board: 4 copper layers, 139 parts (0 on the bottom side), 89 nets, no tracks yet.

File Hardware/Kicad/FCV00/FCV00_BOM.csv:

"Qty","References","Value","Footprint","DNP"
"2","C1,C2","10uF 50V X7R","eCapacitor:C_1206_3216Metric",""
"5","C3,C6,C9,C14,C17","100nF 50V","eCapacitor:C_0603_1608Metric",""
"22","C4,C12,C20,C23,C26,C27,C28,C29,C30,C31,C34,C39,C41,C43,C44,C45,C47,C48,C49,C50,C53,C54","100nF","eCapacitor:C_0402_1005Metric",""
"2","C5,C13","2.2uF 50V","eCapacitor:C_0805_2012Metric",""
"1","C7","6.8nF","eCapacitor:C_0402_1005Metric",""
"1","C8","47pF","eCapacitor:C_0402_1005Metric",""
"2","C10,C11","22uF 16V X5R","eCapacitor:C_0805_2012Metric",""
"1","C15","4.7nF","eCapacitor:C_0402_1005Metric",""
"1","C16","33pF","eCapacitor:C_0402_1005Metric",""
"2","C18,C19","22uF 25V X5R","eCapacitor:C_1206_3216Metric",""
"3","C21,C24,C40","1uF 16V","eCapacitor:C_0402_1005Metric",""
"3","C22,C25,C32","4.7uF 10V","eCapacitor:C_0603_1608Metric",""
"2","C33,C42","1uF","eCapacitor:C_0402_1005Metric",""
"2","C35,C36","2.2uF","eCapacitor:C_0402_1005Metric",""
"4","C37,C38,C51,C52","18pF NP0","eCapacitor:C_0402_1005Metric",""
"1","C46","10uF 10V","eCapacitor:C_0603_1608Metric",""
"1","C55","10uF 25V","eCapacitor:C_0805_2012Metric",""
"1","D1","SMAJ28A","eDiodes:SMAJ28A",""
"2","D2,D3","PMEG6045ETPX","eDiodes:PMEG6045ETPX",""
"1","D4","PMEG3020EH","eDiodes:PMEG3020EH",""
"1","D5","KT-0603R","eLED:KT-0603R",""
"1","D6","BLUE","eLED:LED_0603_1608Metric",""
"1","D7","GREEN","eLED:LED_0603_1608Metric",""
"1","D8","USBLC6-2SC6","eDiodes:USBLC6-2SC6",""
"1","D9","1N4148W","eDiodes:1N4148W",""
"1","FB1","BLM15AG601SN1D","eFerrite:BLM15AG601SN1D",""
"1","FB2","BLM18AG601SN1D","eFerrite:BLM18AG601SN1D",""
"1","J1","USB4105-GF-A","eConnector:USB4105-GF-A",""
"1","J2","SM08B-SRSS-TB","eConnector:SM08B-SRSS-TB",""
"1","J3","SM04B-SRSS-TB","eConnector:SM04B-SRSS-TB",""
"3","J4,J6,J7","SM06B-SRSS-TB","eConnector:SM06B-SRSS-TB",""
"1","J5","SM03B-SRSS-TB","eConnector:SM03B-SRSS-TB",""
"1","L1","SRP5030T-6R8M","eCoil:SRP5030T-6R8M",""
"1","L2","SRP5030T-100M","eCoil:SRP5030T-100M",""
"1","Q1","2N7002","eTransistor:2N7002",""
"2","R1,R12","10k 1%","eResistor:R_0402_1005Metric",""
"1","R2","1k 1%","eResistor:R_0402_1005Metric",""
"1","R3","470k","eResistor:R_0402_1005Metric",""
"2","R4,R34","100k","eResistor:R_0402_1005Metric",""
"2","R5,R9","121k 1%","eResistor:R_0402_1005Metric",""
"1","R6","16.9k","eResistor:R_0402_1005Metric",""
"1","R7","53.6k 1%","eResistor:R_0402_1005Metric",""
"1","R8","10.2k 1%","eResistor:R_0402_1005Metric",""
"1","R10","24.9k","eResistor:R_0402_1005Metric",""
"1","R11","115k 1%","eResistor:R_0402_1005Metric",""
"5","R13,R16,R17,R31,R33","1k","eResistor:R_0402_1005Metric",""
"8","R14,R15,R20,R22,R25,R26,R27,R28","10k","eResistor:R_0402_1005Metric",""
"2","R18,R19","5.1k","eResistor:R_0402_1005Metric",""
"1","R21","20k","eResistor:R_0402_1005Metric",""
"2","R23,R24","2.2k","eResistor:R_0402_1005Metric",""
"1","R29","75R 1%","eResistor:R_0402_1005Metric",""
"1","R30","0R","eResistor:R_0402_1005Metric","DNP"
"1","R32","33R","eResistor:R_0402_1005Metric",""
"1","SW1","B3U-1000P","eSwitch:B3U-1000P",""
"2","U1,U2","TPS54360BDDAR","eConverterDCDC:TPS54360BDDAR",""
"2","U3,U4","AP2112K-3.3TRG1","eLinearReg:AP2112K-3.3TRG1",""
"1","U5","STM32F405RGT6","eMCU:STM32F405RGT6",""
"1","U6","ICM-42688-P","eSensor:ICM-42688-P",""
"1","U7","LPS22DFTR","eSensor:LPS22DFTR",""
"1","U8","W25Q128JVSIQ","eMemory:W25Q128JVSIQ",""
"1","U9","AT7456E","eDisplay:AT7456E",""
"1","Y1","X322508MLB4SI","eCrystal:X322508MLB4SI",""
"1","Y2","X322527MOB4SI","eCrystal:X322527MOB4SI",""

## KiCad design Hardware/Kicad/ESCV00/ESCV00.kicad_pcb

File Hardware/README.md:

# Drone

# Custom Flight Controller PCB

This directory contains the KiCad projects for all the drone electronics, designed at chip level (no plug-and-play modules):

*   `Kicad/FCV00` - Flight Controller
*   `Kicad/ESCV00` - 4-in-1 ESC (AM32)
*   `Kicad/RXV00` - ExpressLRS 2.4 GHz receiver
*   `Kicad/VTXV00` - 5.8 GHz analog video transmitter

See `Kicad/Readme.md` for the block diagram, component choices, library installation and the list of items to verify before ordering boards.

The flight controller specifications are below.

## Hardware Specifications

*   **Form Factor:** 30.5 x 30.5 mm mounting pattern (Standard 5-inch stack).
*   **Microcontroller:** STM32F405RGT6 (168 MHz Cortex-M4F, 1 MB flash).
*   **IMU (Gyro/Accel):** TDK InvenSense ICM-42688-P on a dedicated **SPI1** bus with its own LDO and external 32 kHz CLKIN.
*   **Barometer:** ST LPS22DF (I2C1).
*   **Blackbox:** Winbond W25Q128JV 16 MB SPI flash (SPI3).
*   **OSD:** AT7456E chip on SPI2 for analog video telemetry overlay.
*   **Power Supply (BEC):** 
    *   Input: 6S LiPo (up to 25.2V).
    *   Step-down buck converters (TI TPS54360B, 60 V rated): 5V/3A (ELRS Rx, VTx, GPS, LEDs, USB) and 10V/2A (camera / HD VTx).
    *   3.3V: two AP2112K LDOs from 5V (one dedicated to the IMU).

## Pinout & Connectivity

The PCB is designed with the following I/O in mind:
*   **8-pin ESC Connector:** Carries GND, VBAT (Input), Current Sensor (ADC in), and 4x Motor Signals (DShot/PWM out).
*   **UART 1:** ExpressLRS Receiver (CRSF Protocol).
*   **UART 2 / SPI:** Video Transmitter (VTx) control / OSD.
*   **UART 3:** GPS / Compass (for future expansions).
*   **UART 4 / UART 5 TX:** AUX port.  **UART 5 RX:** ESC telemetry.
*   **USB-C:** configuration and DFU (BOOT button).
*   **I2C:** Reserved for external barometers or slow sensors.

## Design Considerations
*   **EMI Shielding:** The IMU is placed away from high-current ESC traces to minimize electromagnetic interference.
*   **Vibration Isolation:** The board must be mounted using rubber dampeners (gummies) to protect the gyro from motor noise.
*   **Decoupling:** Ample decoupling capacitors are placed near the STM32 and IMU to ensure clean power delivery.

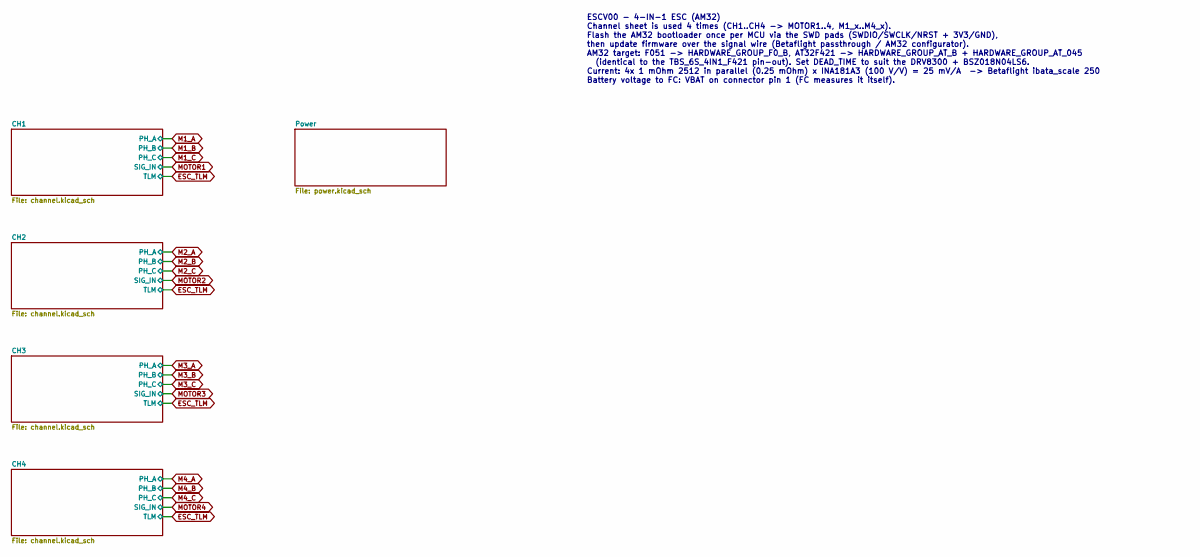
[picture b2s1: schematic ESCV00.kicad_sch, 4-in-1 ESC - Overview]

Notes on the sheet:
ESCV00 - 4-IN-1 ESC (AM32) Channel sheet is used 4 times (CH1..CH4 -> MOTOR1..4, M1_x..M4_x). Flash the AM32 bootloader once per MCU via the SWD pads (SWDIO/SWCLK/NRST + 3V3/GND), then update firmware over the signal wire (Betaflight passthrough / AM32 configurator). AM32 target: F051 -> HARDWARE_G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
